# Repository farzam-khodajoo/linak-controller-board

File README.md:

## Introduction

Linak Controller Board is a small form factor pcb design which features ESP8266 for WIFI communication, this board is designed to control Hospital Bed with quad DC motors. 
(Kicad V6)

Each Motor uses 2 relays to change polarity and reverse rotation, also a linear voltage regulator is featured to power NodeMcu v3 board with small SPI pin connector on the side as extra utiltiy.

you can download schematic [here](https://github.com/farzam-khodajoo/linak-controller-board/blob/master/prints/Linak-controller.pdf).

## 3D views

## PCB

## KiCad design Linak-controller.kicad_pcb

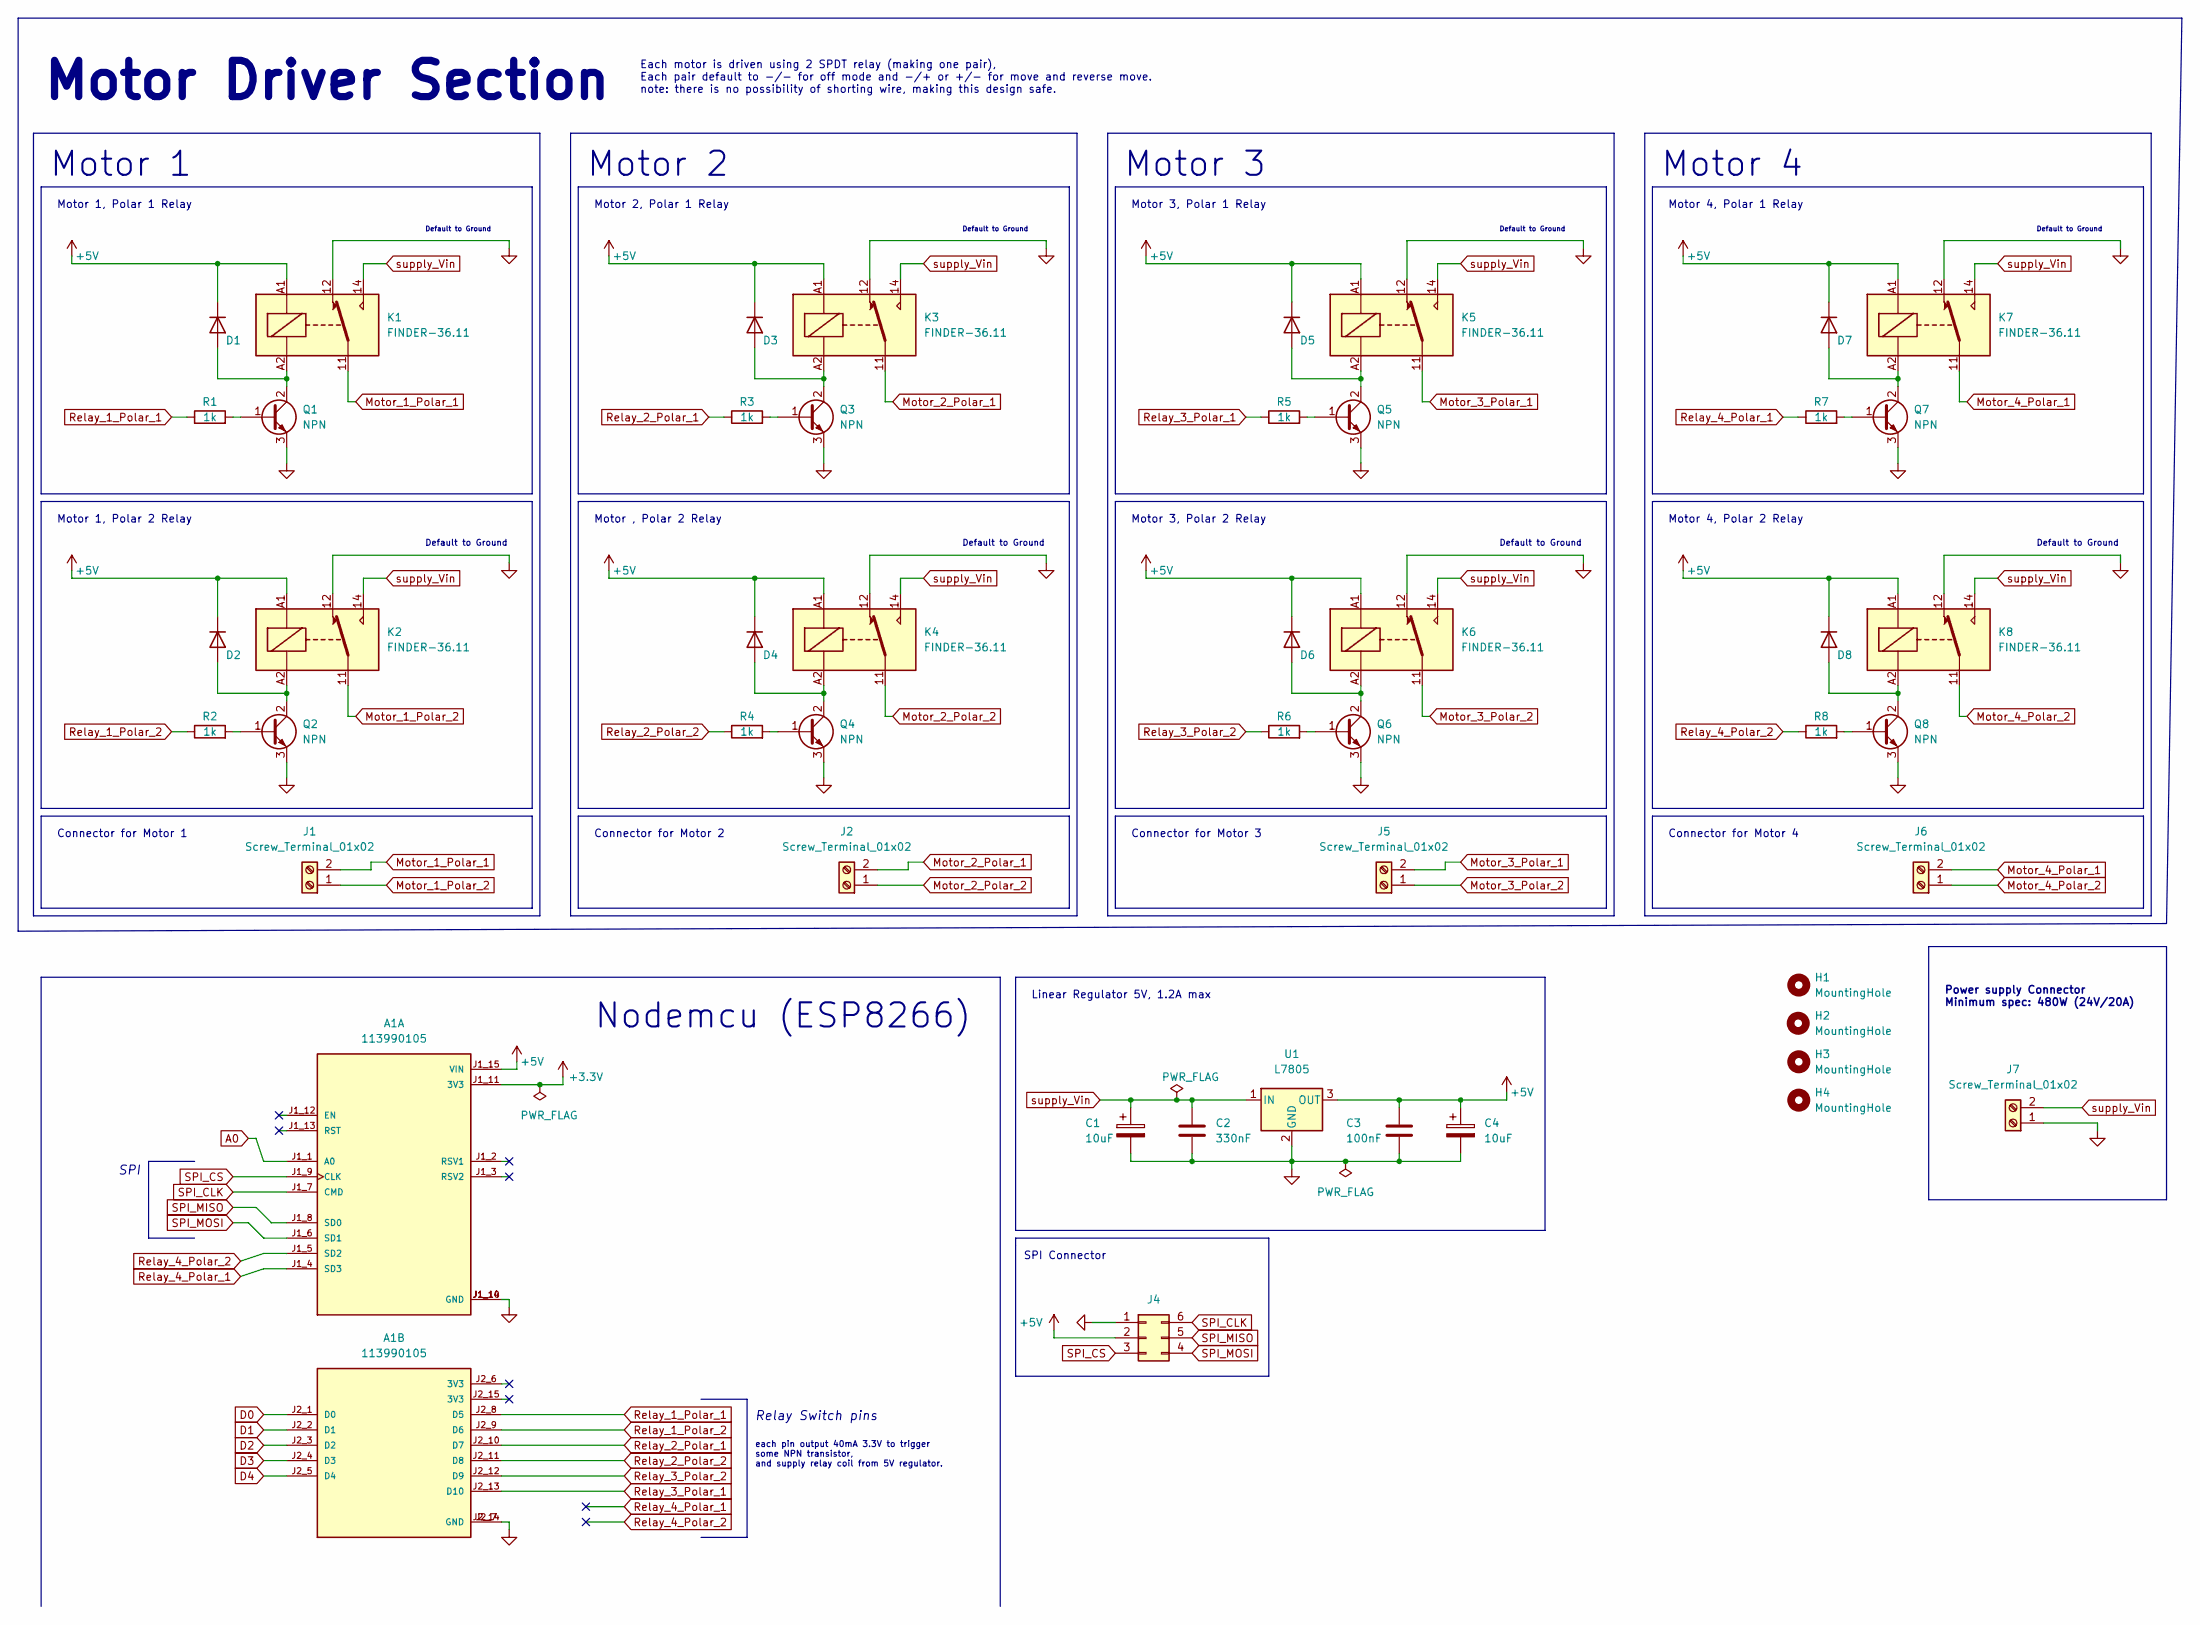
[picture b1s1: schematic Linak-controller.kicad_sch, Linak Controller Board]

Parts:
A1: 113990105; SEEED_NodemcuV3; PARTREV N/A
C1, C4: 10uF; CP_Elec_10x7.9
C2: 330nF; C_1210_3225Metric_Pad1.33x2.70mm_HandSolder
C3: 100nF; C_1210_3225Metric_Pad1.33x2.70mm_HandSolder
D1, D2, D3, D4, D5, D6, D7, D8: 1N914WT; D_SOD-523
H1, H2, H3, H4: MountingHole; MountingHole_2.2mm_M2_DIN965_Pad
J1, J2, J5, J6, J7: Screw_Terminal_01x02; TerminalBlock_Phoenix_MKDS-1,5-2_1x02_P5.00mm_Horizontal
J4: Conn_02x03_Counter_Clockwise; PinHeader_2x03_P2.00mm_Vertical
K1, K2, K3, K4, K5, K6, K7, K8: FINDER-36.11; Relay_SPDT_Finder_36.11
Q1, Q2, Q3, Q4, Q5, Q6, Q7, Q8: NPN; SOT-23
R1, R2, R3, R4, R5, R6, R7, R8: 1k; R_2010_5025Metric_Pad1.40x2.65mm_HandSolder
U1: L7805; TO-252-2

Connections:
+3.3V: A1.J1_11 (3V3)
+5V: A1.J1_15 (VIN), C3.1, C4.1, D1.1 (K), D2.1 (K), D3.1 (K), D4.1 (K), D5.1 (K), D6.1 (K), D7.1 (K), D8.1 (K), J4.2, K1.A1, K2.A1, K3.A1, K4.A1, K5.A1, K6.A1, K7.A1, K8.A1, U1.3 (OUT)
A0: A1.J1_1 (A0)
D0: A1.J2_1 (D0)
D1: A1.J2_2 (D1)
D2: A1.J2_3 (D2)
D3: A1.J2_4 (D3)
D4: A1.J2_5 (D4)
GND: A1.J1_10 (GND), A1.J1_14 (GND), A1.J2_7 (GND), A1.J2_14 (GND), C1.2, C2.2, C3.2, C4.2, J4.1, J7.1, K1.12, K2.12, K3.12, K4.12, K5.12, K6.12, K7.12, K8.12, Q1.3 (E), Q2.3 (E), Q3.3 (E), Q4.3 (E), Q5.3 (E), Q6.3 (E), Q7.3 (E), Q8.3 (E), U1.2 (GND)
Motor_1_Polar_1: J1.2, K1.11
Motor_1_Polar_2: J1.1, K2.11
Motor_2_Polar_1: J2.2, K3.11
Motor_2_Polar_2: J2.1, K4.11
Motor_3_Polar_1: J5.2, K5.11
Motor_3_Polar_2: J5.1, K6.11
Motor_4_Polar_1: J6.2, K7.11
Motor_4_Polar_2: J6.1, K8.11
unnamed: D1.2 (A), K1.A2, Q1.2 (C)
unnamed: D2.2 (A), K2.A2, Q2.2 (C)
unnamed: D3.2 (A), K3.A2, Q3.2 (C)
unnamed: D4.2 (A), K4.A2, Q4.2 (C)
unnamed: D5.2 (A), K5.A2, Q5.2 (C)
unnamed: D6.2 (A), K6.A2, Q6.2 (C)
unnamed: D7.2 (A), K7.A2, Q7.2 (C)
unnamed: D8.2 (A), K8.A2, Q8.2 (C)
unnamed: Q1.1 (B), R1.2
unnamed: Q2.1 (B), R2.2
unnamed: Q3.1 (B), R3.2
unnamed: Q4.1 (B), R4.2
unnamed: Q5.1 (B), R5.2
unnamed: Q6.1 (B), R6.2
unnamed: Q7.1 (B), R7.2
unnamed: Q8.1 (B), R8.2
Relay_1_Polar_1: A1.J2_8 (D5), R1.1
Relay_1_Polar_2: A1.J2_9 (D6), R2.1
Relay_2_Polar_1: A1.J2_10 (D7), R3.1
Relay_2_Polar_2: A1.J2_11 (D8), R4.1
Relay_3_Polar_1: A1.J2_13 (D10), R5.1
Relay_3_Polar_2: A1.J2_12 (D9), R6.1
Relay_4_Polar_1: A1.J1_4 (SD3), R7.1
Relay_4_Polar_2: A1.J1_5 (SD2), R8.1
SPI_CLK: A1.J1_7 (CMD), J4.6
SPI_CS: A1.J1_9 (CLK), J4.3
SPI_MISO: A1.J1_8 (SD0), J4.5
SPI_MOSI: A1.J1_6 (SD1), J4.4
supply_Vin: C1.1, C2.1, J7.2, K1.14, K2.14, K3.14, K4.14, K5.14, K6.14, K7.14, K8.14, U1.1 (IN)

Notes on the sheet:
Motor 3, Polar 1 Relay
Motor 3
Connector for Motor 1
Motor 1
Motor 1, Polar 1 Relay
Each motor is driven using 2 SPDT relay (making one pair), Each pair default to -/- for off mode and -/+ or +/- for move and reverse move. note: there is no possibility of shorting wire, making this design safe.
Relay Switch pins
SPI Connector
Motor , Polar 2 Relay
Motor Driver Section
Default to Ground
Motor 2, Polar 1 Relay
Connector for Motor 4
Motor 4
Nodemcu (ESP8266)
Connector for Motor 2
SPI
Motor 1, Polar 2 Relay
Connector for Motor 3
Motor 4, Polar 1 Relay
Motor 3, Polar 2 Relay
Power supply Connector Minimum spec: 480W (24V/20A)
Linear Regulator 5V, 1.2A max
Motor 4, Polar 2 Relay
each pin output 40mA 3.3V to trigger some NPN transistor, and supply relay coil from 5V regulator.
Motor 2

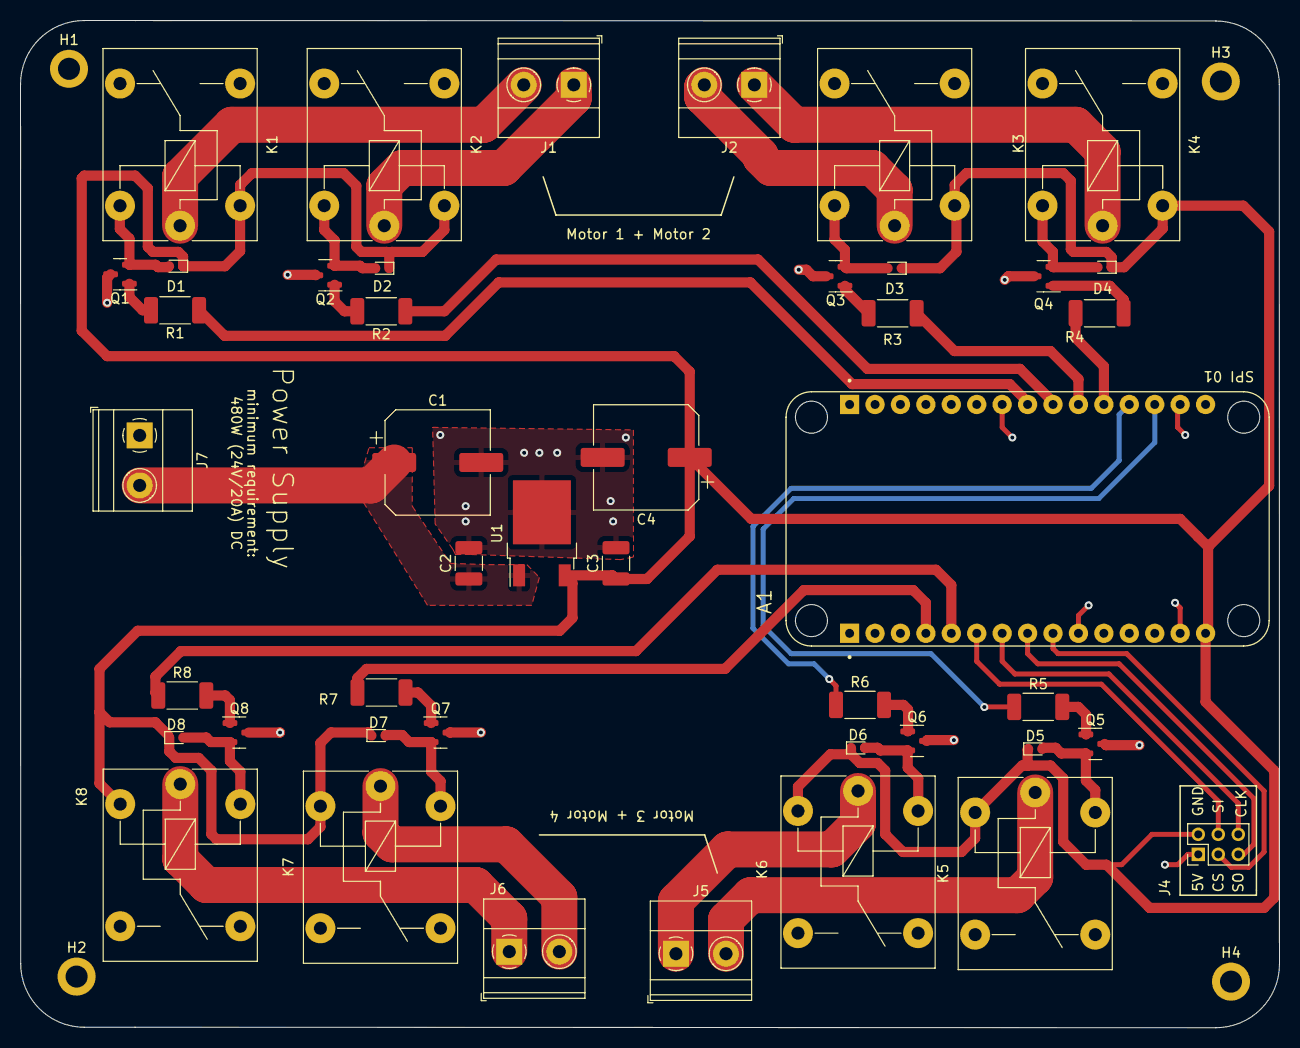
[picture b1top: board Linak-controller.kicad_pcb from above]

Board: 4 copper layers, 125.8 x 100.6 mm, 48 parts (0 on the bottom side), 39 nets.

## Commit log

2023-07-14 fix lazy mistakes
2023-07-16 fix some imperfections
2023-07-16 update pcb image
2023-07-21 Update README.md
    fix typo
